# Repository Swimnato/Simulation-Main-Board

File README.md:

# Simulation Main Board
A universal board for creating simulation panels for the Christa McCaullife Space Center. Created and maintained by NF 2025.

For getting started with the library please visit the [Library Guide](Library%20Guide.md)

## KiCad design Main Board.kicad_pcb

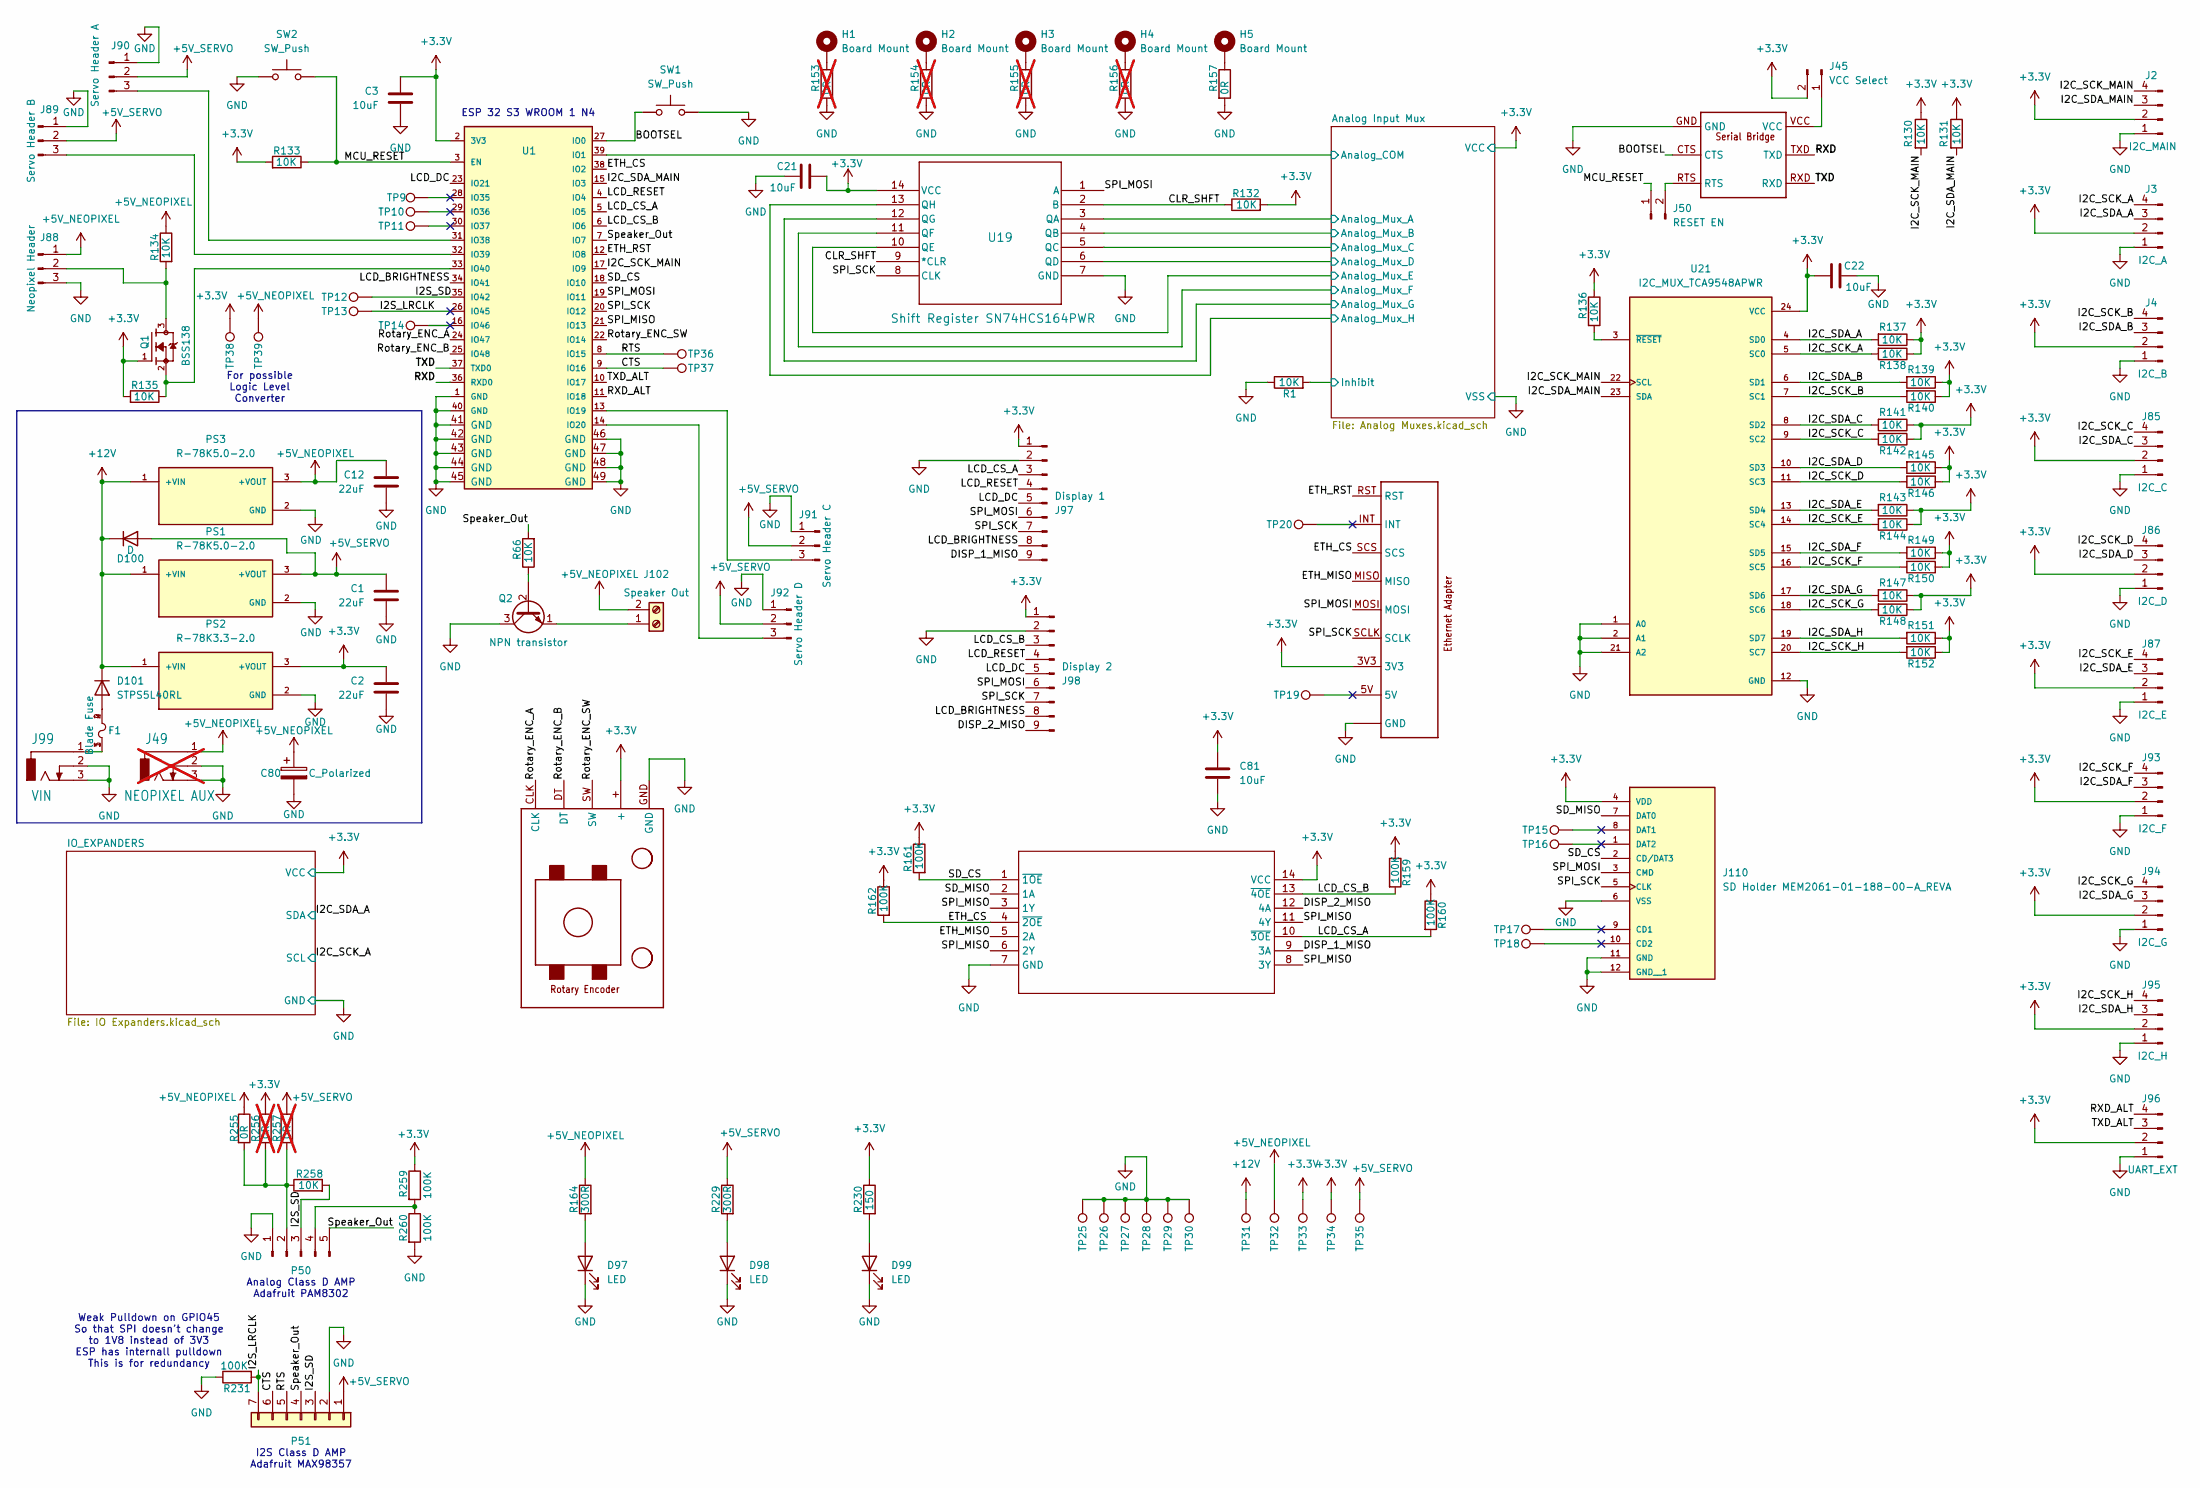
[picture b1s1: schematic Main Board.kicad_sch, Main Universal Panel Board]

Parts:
C1, C2, C12: 22uF; C_0805_2012Metric_Pad1.18x1.45mm_HandSolder
C3, C21, C22, C81: 10uF; C_0805_2012Metric_Pad1.18x1.45mm_HandSolder
C80: C_Polarized; CP_Radial_D10.0mm_P2.50mm_P5.00mm
D97, D98, D99: LED; LED_D5.0mm
D100: D; D_DO-15_P10.16mm_Horizontal
D101: STPS5L40RL; D_DO-201AD_P15.24mm_Horizontal
F1: Blade Fuse; FUSE_3568; PARTREV C
H1, H2, H3, H4, H5: Board Mount; MountingHole_4.3mm_M4_Pad
J1: UART_FTDI
J2: I2C_MAIN; JST_EH_B4B-EH-A_1x04_P2.50mm_Vertical
J3: I2C_A; JST_EH_B4B-EH-A_1x04_P2.50mm_Vertical
J4: I2C_B; JST_EH_B4B-EH-A_1x04_P2.50mm_Vertical
J45: VCC Select; PinHeader_1x02_P2.54mm_Vertical
J49: NEOPIXEL AUX; BarrelJack_Horizontal; not fitted
J50: RESET EN; PinHeader_1x02_P2.54mm_Vertical
J85: I2C_C; JST_EH_B4B-EH-A_1x04_P2.50mm_Vertical
J86: I2C_D; JST_EH_B4B-EH-A_1x04_P2.50mm_Vertical
J87: I2C_E; JST_EH_B4B-EH-A_1x04_P2.50mm_Vertical
J88: Neopixel Header; TerminalBlock_bornier-3_P5.08mm
J89: Servo Header B; PinHeader_1x03_P2.54mm_Vertical
J90: Servo Header A; PinHeader_1x03_P2.54mm_Vertical
J91: Servo Header C; PinHeader_1x03_P2.54mm_Vertical
J92: Servo Header D; PinHeader_1x03_P2.54mm_Vertical
J93: I2C_F; JST_EH_B4B-EH-A_1x04_P2.50mm_Vertical
J94: I2C_G; JST_EH_B4B-EH-A_1x04_P2.50mm_Vertical
J95: I2C_H; JST_EH_B4B-EH-A_1x04_P2.50mm_Vertical
J96: UART_EXT; JST_EH_B4B-EH-A_1x04_P2.50mm_Vertical
J97: Display 1; JST_EH_B9B-EH-A_1x09_P2.50mm_Vertical
J98: Display 2; JST_EH_B9B-EH-A_1x09_P2.50mm_Vertical
J99: VIN; BarrelJack_Horizontal
J102: Speaker Out; TerminalBlock_Phoenix_MKDS-3-2-5.08_1x02_P5.08mm_Horizontal
J110: SD Holder MEM2061-01-188-00-A_REVA; MicroSD Holder; Manufacturer Part Number MEM2061-01-188-00-A
J111: Rotary_Encoder_Header
P50: Conn_01x05_Pin; PinHeader_1x05_P2.54mm_Vertical
P51: Conn_01x07; PinHeader_1x07_P2.54mm_Vertical
PS1, PS3: R-78K5.0-2.0; CONV_R-78K5.0-2.0; PARTREV 0/2023
PS2: R-78K3.3-2.0; CONV_R-78K3.3-2.0; PARTREV 0/2023
Q1: BSS138; SOT95P240X111-3N; PARTREV 30 Jan 2018
Q2: NPN transistor; TO-92_Inline
R1, R66, R130, R131, R132, R133, R134, R135, R136, R137, R138, R139, R140, R141, R142, R143, R144, R145, R146, R147, R148, R149, R150, R151, R152, R258: 10K; R_0603_1608Metric
R153, R154, R155, R156, R256, R257: 0R; R_0603_1608Metric; not fitted
R157, R255: 0R; R_0603_1608Metric
R159, R160, R161, R162, R231, R259, R260: 100K; R_0603_1608Metric
R164, R229: 300R; R_0603_1608Metric
R230: 150; R_0603_1608Metric
SW1, SW2: SW_Push; SW_PUSH_6mm
TP9, TP10, TP11, TP12, TP13, TP14, TP15, TP16, TP17, TP18, TP19, TP20, TP25, TP26, TP27, TP28, TP29, TP30, TP31, TP32, TP33, TP34, TP35, TP36, TP37, TP38, TP39: TestPoint; Pin_D1.0mm_L10.0mm
U1: ESP32-S3-WROOM-1-N4; ESP32S3WROOM1N8R2; MANUFACTURER_PART_NUMBER ESP32-S3-WROOM-1-N4
U19: Shift Register SN74HCS164PWR; TSSOP14_PW_TEX; Manufacturer Part Number SN74HCS164PWR
U21: I2C_MUX_TCA9548APWR; 24-TSSOP_(4.4mm); PARTREV G
U22: Ethernet Adapter; W5500 Ethernet Module
U30: SO14_DIO; Manufacturer Part Number 74HC125D,653

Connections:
+3.3V: C2.1, C3.1, C21.1, C22.1, C81.2, J2.2, J3.2, J4.2, J45.2, J85.2, J86.2, J87.2, J93.2, J94.2, J95.2, J96.2, J97.1, J98.1, J110.4 (VDD), J111.+, PS2.3 (+VOUT), Q1.1, R130.1, R131.1, R132.2, R133.2, R135.2, R136.1, R137.1, R138.1, R139.1, R140.1, R141.1, R142.1, R143.1, R144.1, R145.1, R146.1, R147.1, R148.1, R149.1, R150.1, R151.1, R152.1, R159.1, R160.1, R161.1, R162.1, R230.1, R256.1, R259.1, TP33.1, TP34.1, TP38.1, U1.2 (3V3), U19.14 (VCC), U21.24 (VCC), U22.3V3, U30.14 (VCC); also elsewhere on the board
+5V_NEOPIXEL: C12.1, C80.1, J49.1, J88.1, J102.2, PS3.3 (+VOUT), R134.1, R164.1, R255.1, TP32.1, TP39.1
+5V_SERVO: C1.1, D100.2 (A), J89.2, J90.2, J91.2, J92.2, P51.1, PS1.3 (+VOUT), R229.1, R257.1, TP35.1
+12V: D100.1 (K), D101.1 (K), PS1.1 (+VIN), PS2.1 (+VIN), PS3.1 (+VIN), TP31.1
/Analog Input Mux/Analog_COM: U1.39 (IO1); also elsewhere on the board
/Analog Input Mux/Analog_Mux_A: U19.3 (QA); also elsewhere on the board
/Analog Input Mux/Analog_Mux_B: U19.4 (QB); also elsewhere on the board
/Analog Input Mux/Analog_Mux_C: U19.5 (QC); also elsewhere on the board
/Analog Input Mux/Analog_Mux_D: U19.6 (QD); also elsewhere on the board
/Analog Input Mux/Analog_Mux_E: U19.10 (QE); also elsewhere on the board
/Analog Input Mux/Analog_Mux_F: U19.11 (QF); also elsewhere on the board
/Analog Input Mux/Analog_Mux_G: U19.12 (QG); also elsewhere on the board
/Analog Input Mux/Analog_Mux_H: U19.13 (QH); also elsewhere on the board
/Analog Input Mux/Inhibit: R1.2; also elsewhere on the board
/BOOTSEL: J1.CTS, SW1.1, U1.27 (IO0)
/CLR_SHFT: R132.1, U19.2 (B), U19.9 (*CLR)
/CTS: P51.6, TP37.1, U1.9 (IO16)
/DISP_1_MISO: J97.9, U30.9 (3A)
/DISP_2_MISO: J98.9, U30.12 (4A)
/ETH_CS: R162.2, U1.38 (IO2), U22.SCS, U30.4 (~2OE)
/ETH_MISO: U22.MISO, U30.5 (2A)
/ETH_RST: U1.12 (IO8), U22.RST
/I2C_SCK_A: J3.4, R138.2, U21.5 (SC0); also elsewhere on the board
/I2C_SCK_B: J4.4, R140.2, U21.7 (SC1)
/I2C_SCK_C: J85.4, R142.2, U21.9 (SC2)
/I2C_SCK_D: J86.4, R146.2, U21.11 (SC3)
/I2C_SCK_E: J87.4, R144.2, U21.14 (SC4)
/I2C_SCK_F: J93.4, R150.2, U21.16 (SC5)
/I2C_SCK_G: J94.4, R148.2, U21.18 (SC6)
/I2C_SCK_H: J95.4, R152.2, U21.20 (SC7)
/I2C_SCK_MAIN: J2.4, R130.2, U1.17 (IO9), U21.22 (SCL)
/I2C_SDA_A: J3.3, R137.2, U21.4 (SD0); also elsewhere on the board
/I2C_SDA_B: J4.3, R139.2, U21.6 (SD1)
/I2C_SDA_C: J85.3, R141.2, U21.8 (SD2)
/I2C_SDA_D: J86.3, R145.2, U21.10 (SD3)
/I2C_SDA_E: J87.3, R143.2, U21.13 (SD4)
/I2C_SDA_F: J93.3, R149.2, U21.15 (SD5)
/I2C_SDA_G: J94.3, R147.2, U21.17 (SD6)
/I2C_SDA_H: J95.3, R151.2, U21.19 (SD7)
/I2C_SDA_MAIN: J2.3, R131.2, U1.15 (IO3), U21.23 (SDA)
/I2S_LRCLK: P51.7, R231.2, TP13.1, U1.26 (IO45)
/I2S_SD: P50.3, P51.3, R258.2, TP12.1, U1.35 (IO42)
/LCD_BRIGHTNESS: J97.8, J98.8, U1.34 (IO41)
/LCD_CS_A: J97.3, R160.2, U1.5 (IO5), U30.10 (~3OE)
/LCD_CS_B: J98.3, R159.2, U1.6 (IO6), U30.13 (~4OE)
/LCD_DC: J97.5, J98.5, U1.23 (IO21)
/LCD_RESET: J97.4, J98.4, U1.4 (IO4)
/MCU_RESET: J50.1, R133.1, SW2.1, U1.3 (EN)
/RTS: P51.5, TP36.1, U1.8 (IO15)
/RXD: J1.TXD, U1.36 (RXD0)
/RXD_ALT: J96.4, U1.11 (IO18)
/Rotary_ENC_A: J111.CLK, U1.24 (IO47)
/Rotary_ENC_B: J111.DT, U1.25 (IO48)
/Rotary_ENC_SW: J111.SW, U1.22 (IO14)
/SD_CS: J110.2 (CD/DAT3), R161.2, U1.18 (IO10), U30.1 (~1OE)
/SD_MISO: J110.7 (DAT0), U30.2 (1A)
/SPI_MISO: U1.21 (IO13), U30.3 (1Y), U30.6 (2Y), U30.8 (3Y), U30.11 (4Y)
/SPI_MOSI: J97.6, J98.6, J110.3 (CMD), U1.19 (IO11), U19.1 (A), U22.MOSI
/SPI_SCK: J97.7, J98.7, J110.5 (CLK), U1.20 (IO12), U19.8 (CLK), U22.SCLK
/Speaker_Out: P50.5, P51.4, R66.2, U1.7 (IO7)
/TXD: J1.RXD, U1.37 (TXD0)
/TXD_ALT: J96.3, U1.10 (IO17)
GND: C1.2, C2.2, C3.2, C12.2, C21.2, C22.2, C80.2, C81.1, D97.1 (K), D98.1 (K), D99.1 (K), J1.GND, J2.1, J3.1, J4.1, J49.2, J49.3, J85.1, J86.1, J87.1, J88.3, J89.1, J90.1, J91.1, J92.1, J93.1, J94.1, J95.1, J96.1, J97.2, J98.2, J99.2, J99.3, J110.6 (VSS), J110.11 (GND), J110.12 (GND__1), J111.GND, P50.1, P51.2, PS1.2 (GND), PS2.2 (GND), PS3.2 (GND), Q2.3 (C), R1.1, R153.2, R154.2, R155.2, R156.2, R157.2, R231.1, R260.2, SW1.2, SW2.2, TP25.1, TP26.1, TP27.1, TP28.1, TP29.1, TP30.1, U1.1 (GND), U1.40 (GND), U1.41 (GND), U1.42 (GND), U1.43 (GND), U1.44 (GND), U1.45 (GND), U1.46 (GND), U1.47 (GND), U1.48 (GND), U1.49 (GND), U19.7 (GND), U21.1 (A0), U21.2 (A1), U21.12 (GND), U21.21 (A2), U22.GND@1 (GND), U22.GND@2 (GND), U30.7 (GND); also elsewhere on the board
unnamed: D97.2 (A), R164.2
unnamed: D98.2 (A), R229.2
unnamed: D99.2 (A), R230.2
unnamed: D101.2 (A), F1.2, F1.4
unnamed: F1.1, F1.3, J99.1
unnamed: H1.1, R153.1
unnamed: H2.1, R154.1
unnamed: H3.1, R155.1
unnamed: H4.1, R156.1
unnamed: H5.1, R157.1
unnamed: J1.VCC, J45.1
unnamed: J1.RTS, J50.2
unnamed: J88.2, Q1.3, R134.2
unnamed: J89.3, U1.32 (IO39)
unnamed: J90.3, U1.31 (IO38)
unnamed: J91.3, U1.13 (IO19)
unnamed: J92.3, U1.14 (IO20)
unnamed: J102.1, Q2.1 (E)
unnamed: P50.2, R255.2, R256.2, R257.2, R258.1
unnamed: P50.4, R259.2, R260.1
unnamed: Q2.2 (B), R66.1
unnamed: Q1.2, R135.1, U1.33 (IO40)
unnamed: R136.2, U21.3 (~RESET)

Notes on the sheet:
ESP 32 S3 WROOM 1 N4
I2S Class D AMP Adafruit MAX98357
For possible Logic Level Converter
Weak Pulldown on GPIO45 So that SPI doesn't change to 1V8 instead of 3V3 ESP has internall pulldown This is for redundancy
Analog Class D AMP Adafruit PAM8302

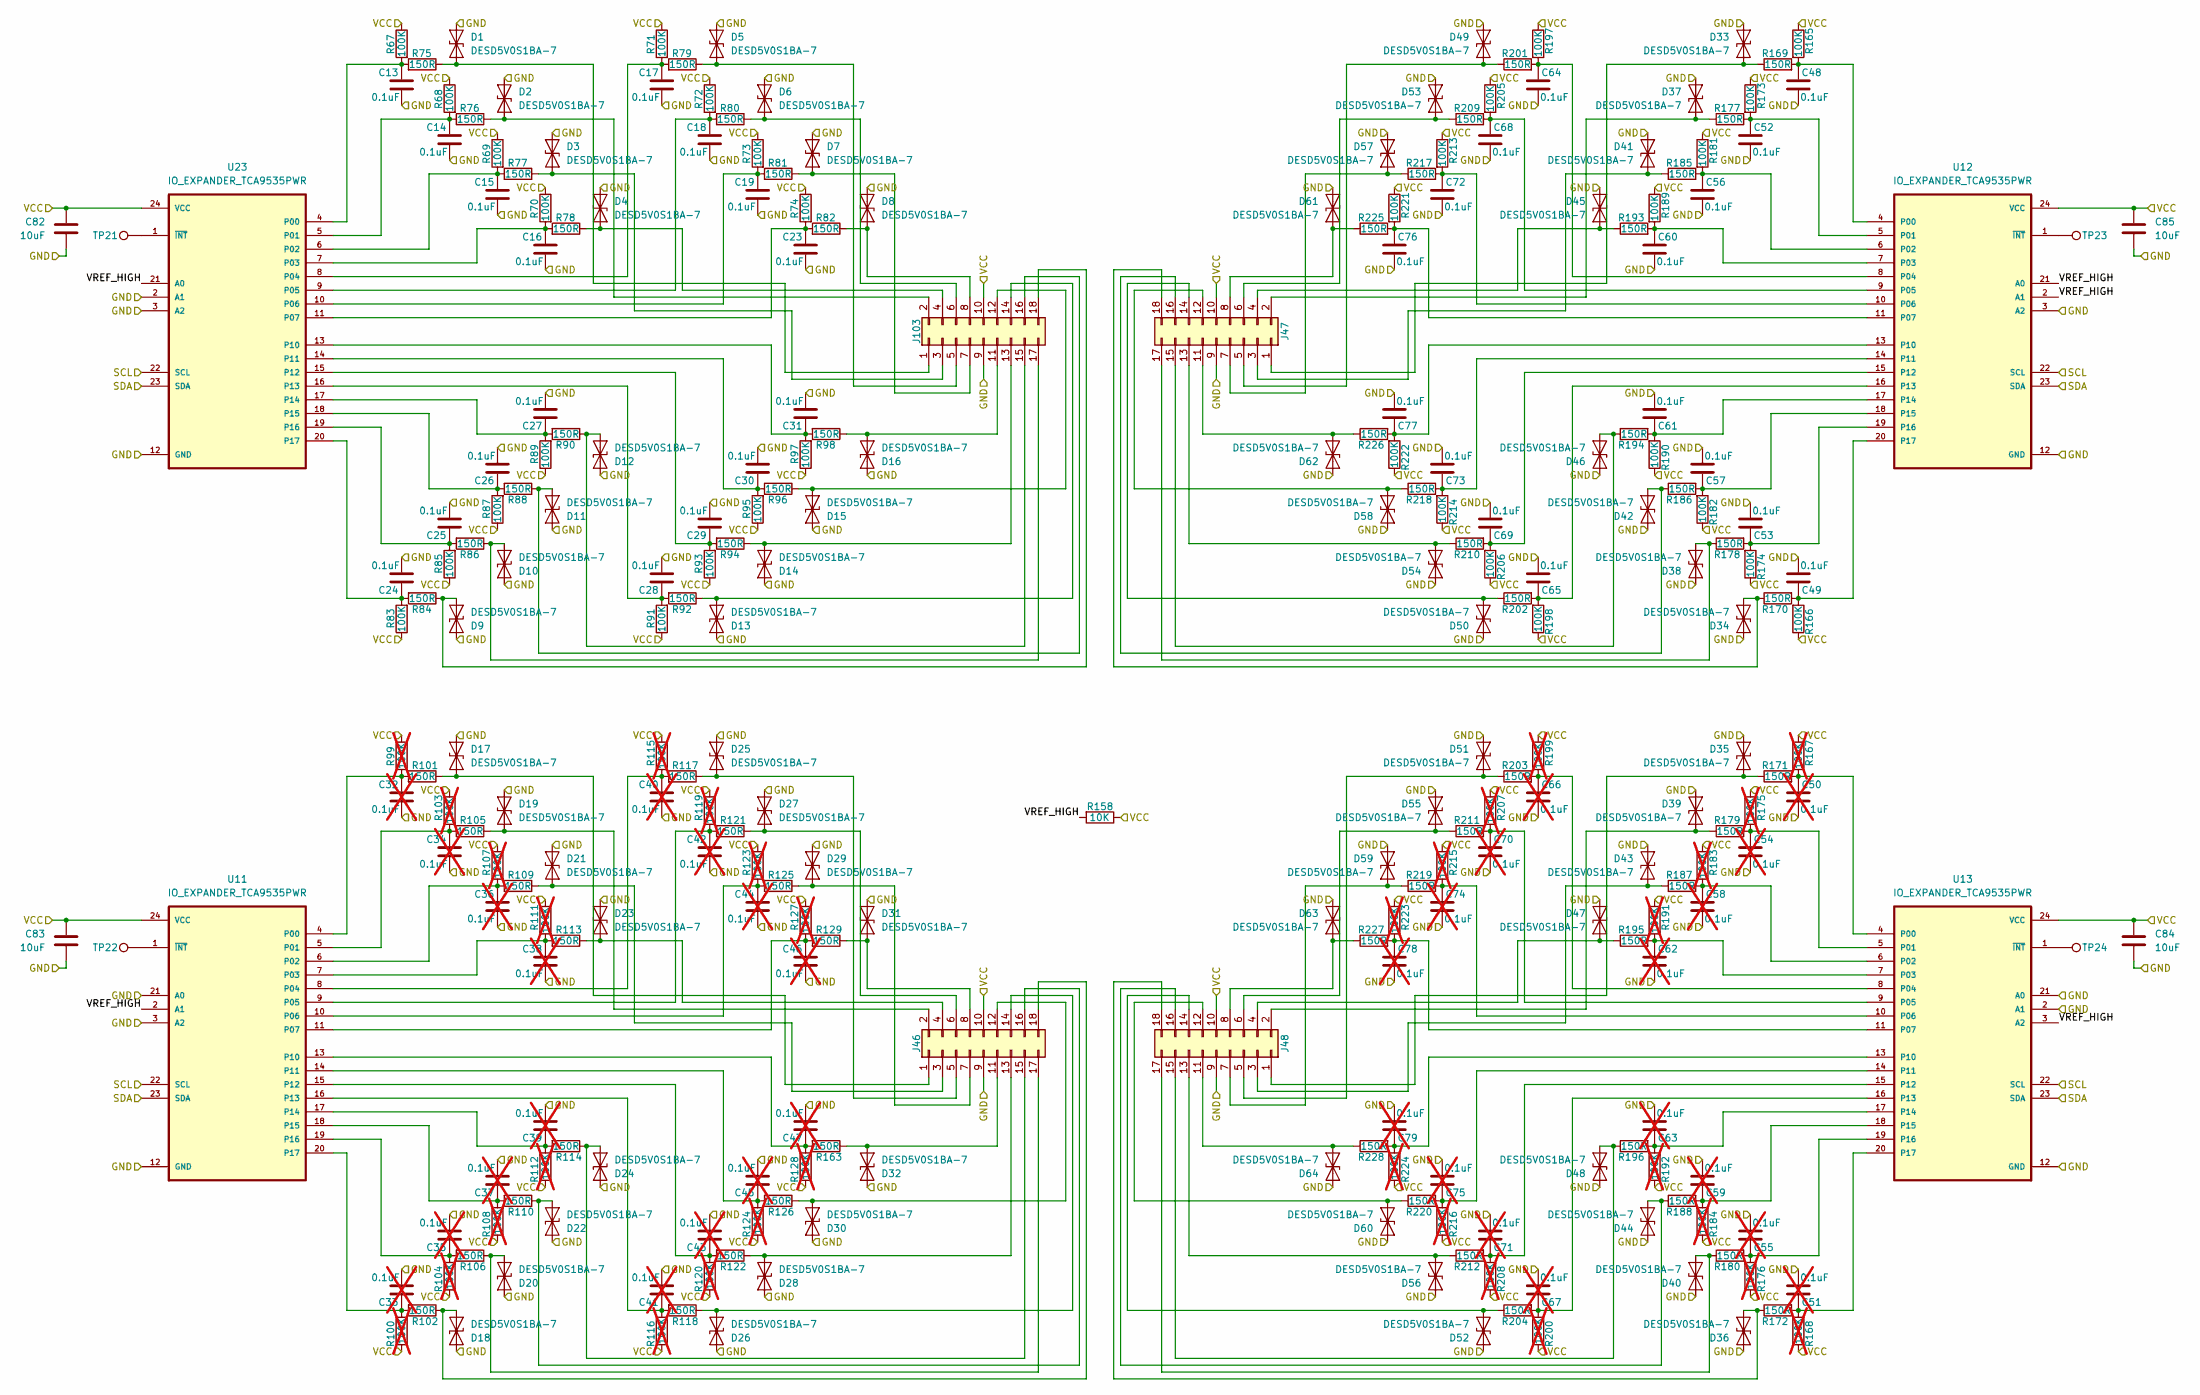
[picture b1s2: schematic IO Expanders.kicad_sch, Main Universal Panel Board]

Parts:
C13, C14, C15, C16, C17, C18, C19, C23, C24, C25, C26, C27, C28, C29, C30, C31, C48, C49, C52, C53, C56, C57, C60, C61, C64, C65, C68, C69, C72, C73, C76, C77: 0.1uF; C_0603_1608Metric_Pad1.08x0.95mm_HandSolder
C32, C33, C34, C35, C36, C37, C38, C39, C40, C41, C42, C43, C44, C45, C46, C47, C50, C51, C54, C55, C58, C59, C62, C63, C66, C67, C70, C71, C74, C75, C78, C79: 0.1uF; C_0603_1608Metric_Pad1.08x0.95mm_HandSolder; not fitted
C82, C83, C84, C85: 10uF; C_0805_2012Metric_Pad1.18x1.45mm_HandSolder
D1, D2, D3, D4, D5, D6, D7, D8, D9, D10, D11, D12, D13, D14, D15, D16, D17, D18, D19, D20, D21, D22, D23, D24, D25, D26, D27, D28, D29, D30, D31, D32, D33, D34, D35, D36, D37, D38, D39, D40, D41, D42, D43, D44, D45, D46, D47, D48, D49, D50, D51, D52, D53, D54, D55, D56, D57, D58, D59, D60, D61, D62, D63, D64: DESD5V0S1BA-7; D_SOD-323
J46, J47, J48, J103: Conn_02x08_Odd_Even; IDC-Header_2x09_P2.54mm_Vertical
R67, R68, R69, R70, R71, R72, R73, R74, R83, R85, R87, R89, R91, R93, R95, R97, R165, R166, R173, R174, R181, R182, R189, R190, R197, R198, R205, R206, R213, R214, R221, R222: 100K; R_0603_1608Metric
R75, R76, R77, R78, R79, R80, R81, R82, R84, R86, R88, R90, R92, R94, R96, R98, R101, R102, R105, R106, R109, R110, R113, R114, R117, R118, R121, R122, R125, R126, R129, R163, R169, R170, R171, R172, R177, R178, R179, R180, R185, R186, R187, R188, R193, R194, R195, R196, R201, R202, R203, R204, R209, R210, R211, R212, R217, R218, R219, R220, R225, R226, R227, R228: 150R; R_0603_1608Metric
R99, R100, R103, R104, R107, R108, R111, R112, R115, R116, R119, R120, R123, R124, R127, R128, R167, R168, R175, R176, R183, R184, R191, R192, R199, R200, R207, R208, R215, R216, R223, R224: 100K; R_0603_1608Metric; not fitted
R158: 10K; R_0603_1608Metric
TP21, TP22, TP23, TP24: TestPoint; Pin_D1.0mm_L10.0mm
U11, U12, U13, U23: IO_EXPANDER_TCA9535PWR; 24-TSSOP_(4.4mm); Manufacturer Part Number TCA9535PWR

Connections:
+3.3V: C82.2, C83.2, C84.2, C85.2, J46.10, J47.10, J48.10, J103.10, R67.1, R68.1, R69.1, R70.1, R71.1, R72.1, R73.1, R74.1, R83.1, R85.1, R87.1, R89.1, R91.1, R93.1, R95.1, R97.1, R99.1, R100.1, R103.1, R104.1, R107.1, R108.1, R111.1, R112.1, R115.1, R116.1, R119.1, R120.1, R123.1, R124.1, R127.1, R128.1, R158.1, R165.1, R166.1, R167.1, R168.1, R173.1, R174.1, R175.1, R176.1, R181.1, R182.1, R183.1, R184.1, R189.1, R190.1, R191.1, R192.1, R197.1, R198.1, R199.1, R200.1, R205.1, R206.1, R207.1, R208.1, R213.1, R214.1, R215.1, R216.1, R221.1, R222.1, R223.1, R224.1, U11.24 (VCC), U12.24 (VCC), U13.24 (VCC), U23.24 (VCC); also elsewhere on the board
/I2C_SCK_A: U11.22 (SCL), U12.22 (SCL), U13.22 (SCL), U23.22 (SCL); also elsewhere on the board
/I2C_SDA_A: U11.23 (SDA), U12.23 (SDA), U13.23 (SDA), U23.23 (SDA); also elsewhere on the board
/IO_EXPANDERS/VREF_HIGH: R158.2, U11.2 (A1), U12.2 (A1), U12.21 (A0), U13.3 (A2), U23.21 (A0)
GND: C13.2, C14.2, C15.2, C16.2, C17.2, C18.2, C19.2, C23.2, C24.2, C25.2, C26.2, C27.2, C28.2, C29.2, C30.2, C31.2, C32.2, C33.2, C34.2, C35.2, C36.2, C37.2, C38.2, C39.2, C40.2, C41.2, C42.2, C43.2, C44.2, C45.2, C46.2, C47.2, C48.2, C49.2, C50.2, C51.2, C52.2, C53.2, C54.2, C55.2, C56.2, C57.2, C58.2, C59.2, C60.2, C61.2, C62.2, C63.2, C64.2, C65.2, C66.2, C67.2, C68.2, C69.2, C70.2, C71.2, C72.2, C73.2, C74.2, C75.2, C76.2, C77.2, C78.2, C79.2, C82.1, C83.1, C84.1, C85.1, D1.2 (A2), D2.2 (A2), D3.2 (A2), D4.2 (A2), D5.2 (A2), D6.2 (A2), D7.2 (A2), D8.2 (A2), D9.2 (A2), D10.2 (A2), D11.2 (A2), D12.2 (A2), D13.2 (A2), D14.2 (A2), D15.2 (A2), D16.2 (A2), D17.2 (A2), D18.2 (A2), D19.2 (A2), D20.2 (A2), D21.2 (A2), D22.2 (A2), D23.2 (A2), D24.2 (A2), D25.2 (A2), D26.2 (A2), D27.2 (A2), D28.2 (A2), D29.2 (A2), D30.2 (A2), D31.2 (A2), D32.2 (A2), D33.2 (A2), D34.2 (A2), D35.2 (A2), D36.2 (A2), D37.2 (A2), D38.2 (A2), D39.2 (A2), D40.2 (A2), D41.2 (A2), D42.2 (A2), D43.2 (A2), D44.2 (A2), D45.2 (A2), D46.2 (A2), D47.2 (A2), D48.2 (A2), D49.2 (A2), D50.2 (A2), D51.2 (A2), D52.2 (A2), D53.2 (A2), D54.2 (A2), D55.2 (A2), D56.2 (A2), D57.2 (A2), D58.2 (A2), D59.2 (A2), D60.2 (A2), D61.2 (A2), D62.2 (A2), D63.2 (A2), D64.2 (A2), J46.9, J47.9, J48.9, J103.9, U11.3 (A2), U11.12 (GND), U11.21 (A0), U12.3 (A2), U12.12 (GND), U13.2 (A1), U13.12 (GND), U13.21 (A0), U23.2 (A1), U23.3 (A2), U23.12 (GND); also elsewhere on the board
unnamed: D1.1 (A1), J103.1, R75.1
unnamed: D2.1 (A1), J103.2, R76.1
unnamed: D3.1 (A1), J103.3, R77.1
unnamed: D4.1 (A1), J103.4, R78.1
unnamed: D5.1 (A1), J103.5, R79.1
unnamed: D6.1 (A1), J103.6, R80.1
unnamed: D7.1 (A1), J103.7, R81.1
unnamed: D8.1 (A1), J103.8, R82.1
unnamed: D9.1 (A1), J103.18, R84.1
unnamed: D10.1 (A1), J103.17, R86.1
unnamed: D11.1 (A1), J103.16, R88.1
unnamed: D12.1 (A1), J103.15, R90.1
unnamed: D13.1 (A1), J103.14, R92.1
unnamed: D14.1 (A1), J103.13, R94.1
unnamed: D15.1 (A1), J103.12, R96.1
unnamed: D16.1 (A1), J103.11, R98.1
unnamed: D17.1 (A1), J46.1, R101.1
unnamed: D18.1 (A1), J46.18, R102.1
unnamed: D19.1 (A1), J46.2, R105.1
unnamed: D20.1 (A1), J46.17, R106.1
unnamed: D21.1 (A1), J46.3, R109.1
unnamed: D22.1 (A1), J46.16, R110.1
unnamed: D23.1 (A1), J46.4, R113.1
unnamed: D24.1 (A1), J46.15, R114.1
unnamed: D25.1 (A1), J46.5, R117.1
unnamed: D26.1 (A1), J46.14, R118.1
unnamed: D27.1 (A1), J46.6, R121.1
unnamed: D28.1 (A1), J46.13, R122.1
unnamed: D29.1 (A1), J46.7, R125.1
unnamed: D30.1 (A1), J46.12, R126.1
unnamed: D31.1 (A1), J46.8, R129.1
unnamed: D32.1 (A1), J46.11, R163.1
unnamed: D33.1 (A1), J47.1, R169.1
unnamed: D34.1 (A1), J47.18, R170.1
unnamed: D35.1 (A1), J48.1, R171.1
unnamed: D36.1 (A1), J48.18, R172.1
unnamed: D37.1 (A1), J47.2, R177.1
unnamed: D38.1 (A1), J47.17, R178.1
unnamed: D39.1 (A1), J48.2, R179.1
unnamed: D40.1 (A1), J48.17, R180.1
unnamed: D41.1 (A1), J47.3, R185.1
unnamed: D42.1 (A1), J47.16, R186.1
unnamed: D43.1 (A1), J48.3, R187.1
unnamed: D44.1 (A1), J48.16, R188.1
unnamed: D45.1 (A1), J47.4, R193.1
unnamed: D46.1 (A1), J47.15, R194.1
unnamed: D47.1 (A1), J48.4, R195.1
unnamed: D48.1 (A1), J48.15, R196.1
unnamed: D49.1 (A1), J47.5, R201.1
unnamed: D50.1 (A1), J47.14, R202.1
unnamed: D51.1 (A1), J48.5, R203.1
unnamed: D52.1 (A1), J48.14, R204.1
unnamed: D53.1 (A1), J47.6, R209.1
unnamed: D54.1 (A1), J47.13, R210.1
unnamed: D55.1 (A1), J48.6, R211.1
unnamed: D56.1 (A1), J48.13, R212.1
unnamed: D57.1 (A1), J47.7, R217.1
unnamed: D58.1 (A1), J47.12, R218.1
unnamed: D59.1 (A1), J48.7, R219.1
unnamed: D60.1 (A1), J48.12, R220.1
unnamed: D61.1 (A1), J47.8, R225.1
unnamed: D62.1 (A1), J47.11, R226.1
unnamed: D63.1 (A1), J48.8, R227.1
unnamed: D64.1 (A1), J48.11, R228.1
unnamed: C32.1, R99.2, R101.2, U11.4 (P00)
unnamed: C34.1, R103.2, R105.2, U11.5 (P01)
unnamed: C36.1, R107.2, R109.2, U11.6 (P02)
unnamed: C38.1, R111.2, R113.2, U11.7 (P03)
unnamed: C40.1, R115.2, R117.2, U11.8 (P04)
unnamed: C42.1, R119.2, R121.2, U11.9 (P05)
unnamed: C44.1, R123.2, R125.2, U11.10 (P06)
unnamed: C46.1, R127.2, R129.2, U11.11 (P07)
unnamed: C47.1, R128.2, R163.2, U11.13 (P10)
unnamed: C45.1, R124.2, R126.2, U11.14 (P11)
unnamed: C43.1, R120.2, R122.2, U11.15 (P12)
unnamed: C41.1, R116.2, R118.2, U11.16 (P13)
unnamed: C39.1, R112.2, R114.2, U11.17 (P14)
unnamed: C37.1, R108.2, R110.2, U11.18 (P15)
unnamed: C35.1, R104.2, R106.2, U11.19 (P16)
unnamed: C33.1, R100.2, R102.2, U11.20 (P17)
unnamed: TP22.1, U11.1 (~INT)
unnamed: C48.1, R165.2, R169.2, U12.4 (P00)
unnamed: C52.1, R173.2, R177.2, U12.5 (P01)
unnamed: C56.1, R181.2, R185.2, U12.6 (P02)
unnamed: C60.1, R189.2, R193.2, U12.7 (P03)
unnamed: C64.1, R197.2, R201.2, U12.8 (P04)
unnamed: C68.1, R205.2, R209.2, U12.9 (P05)
unnamed: C72.1, R213.2, R217.2, U12.10 (P06)
unnamed: C76.1, R221.2, R225.2, U12.11 (P07)
unnamed: C77.1, R222.2, R226.2, U12.13 (P10)
unnamed: C73.1, R214.2, R218.2, U12.14 (P11)
unnamed: C69.1, R206.2, R210.2, U12.15 (P12)
unnamed: C65.1, R198.2, R202.2, U12.16 (P13)
unnamed: C61.1, R190.2, R194.2, U12.17 (P14)
unnamed: C57.1, R182.2, R186.2, U12.18 (P15)
unnamed: C53.1, R174.2, R178.2, U12.19 (P16)
unnamed: C49.1, R166.2, R170.2, U12.20 (P17)
unnamed: TP23.1, U12.1 (~INT)
unnamed: C50.1, R167.2, R171.2, U13.4 (P00)
unnamed: C54.1, R175.2, R179.2, U13.5 (P01)
unnamed: C58.1, R183.2, R187.2, U13.6 (P02)
unnamed: C62.1, R191.2, R195.2, U13.7 (P03)
unnamed: C66.1, R199.2, R203.2, U13.8 (P04)
unnamed: C70.1, R207.2, R211.2, U13.9 (P05)
unnamed: C74.1, R215.2, R219.2, U13.10 (P06)
unnamed: C78.1, R223.2, R227.2, U13.11 (P07)
unnamed: C79.1, R224.2, R228.2, U13.13 (P10)
unnamed: C75.1, R216.2, R220.2, U13.14 (P11)
unnamed: C71.1, R208.2, R212.2, U13.15 (P12)
unnamed: C67.1, R200.2, R204.2, U13.16 (P13)
unnamed: C63.1, R192.2, R196.2, U13.17 (P14)
unnamed: C59.1, R184.2, R188.2, U13.18 (P15)
unnamed: C55.1, R176.2, R180.2, U13.19 (P16)
unnamed: C51.1, R168.2, R172.2, U13.20 (P17)
unnamed: TP24.1, U13.1 (~INT)
unnamed: C13.1, R67.2, R75.2, U23.4 (P00)
unnamed: C14.1, R68.2, R76.2, U23.5 (P01)
unnamed: C15.1, R69.2, R77.2, U23.6 (P02)
unnamed: C16.1, R70.2, R78.2, U23.7 (P03)
unnamed: C17.1, R71.2, R79.2, U23.8 (P04)
unnamed: C18.1, R72.2, R80.2, U23.9 (P05)
unnamed: C19.1, R73.2, R81.2, U23.10 (P06)
unnamed: C23.1, R74.2, R82.2, U23.11 (P07)
unnamed: C31.1, R97.2, R98.2, U23.13 (P10)
unnamed: C30.1, R95.2, R96.2, U23.14 (P11)
unnamed: C29.1, R93.2, R94.2, U23.15 (P12)
unnamed: C28.1, R91.2, R92.2, U23.16 (P13)
unnamed: C27.1, R89.2, R90.2, U23.17 (P14)
unnamed: C26.1, R87.2, R88.2, U23.18 (P15)
unnamed: C25.1, R85.2, R86.2, U23.19 (P16)
unnamed: C24.1, R83.2, R84.2, U23.20 (P17)
unnamed: TP21.1, U23.1 (~INT)
